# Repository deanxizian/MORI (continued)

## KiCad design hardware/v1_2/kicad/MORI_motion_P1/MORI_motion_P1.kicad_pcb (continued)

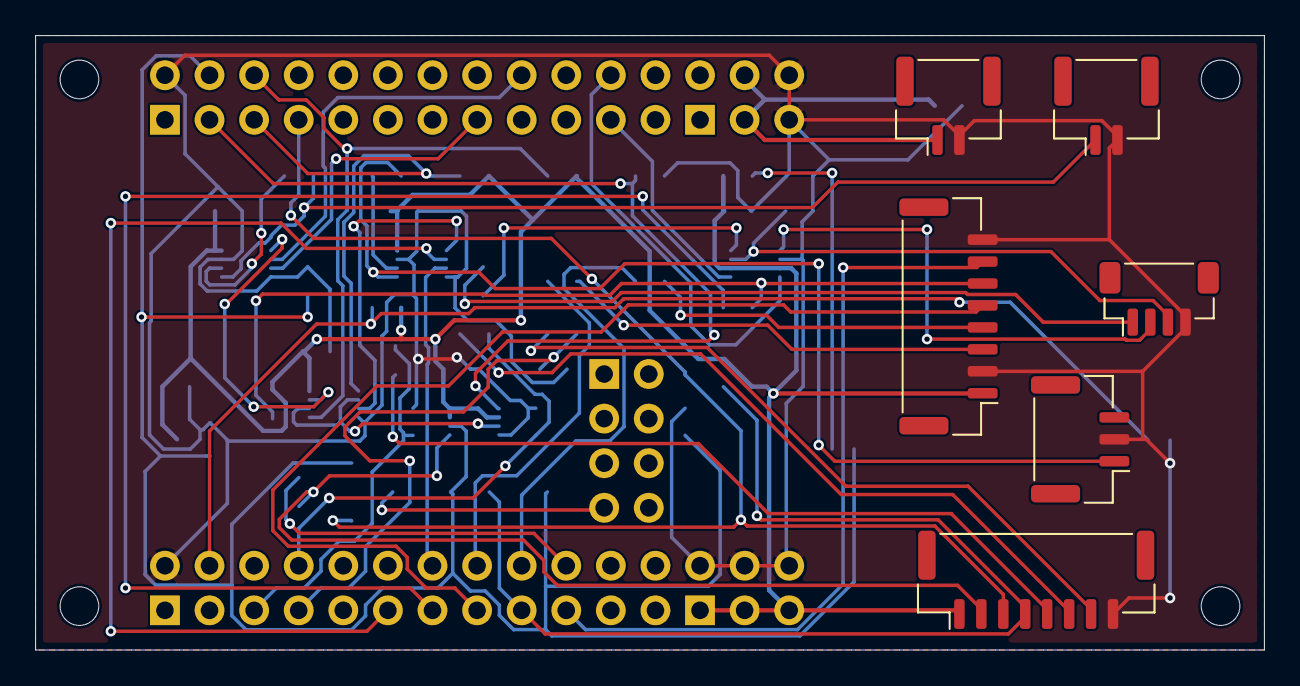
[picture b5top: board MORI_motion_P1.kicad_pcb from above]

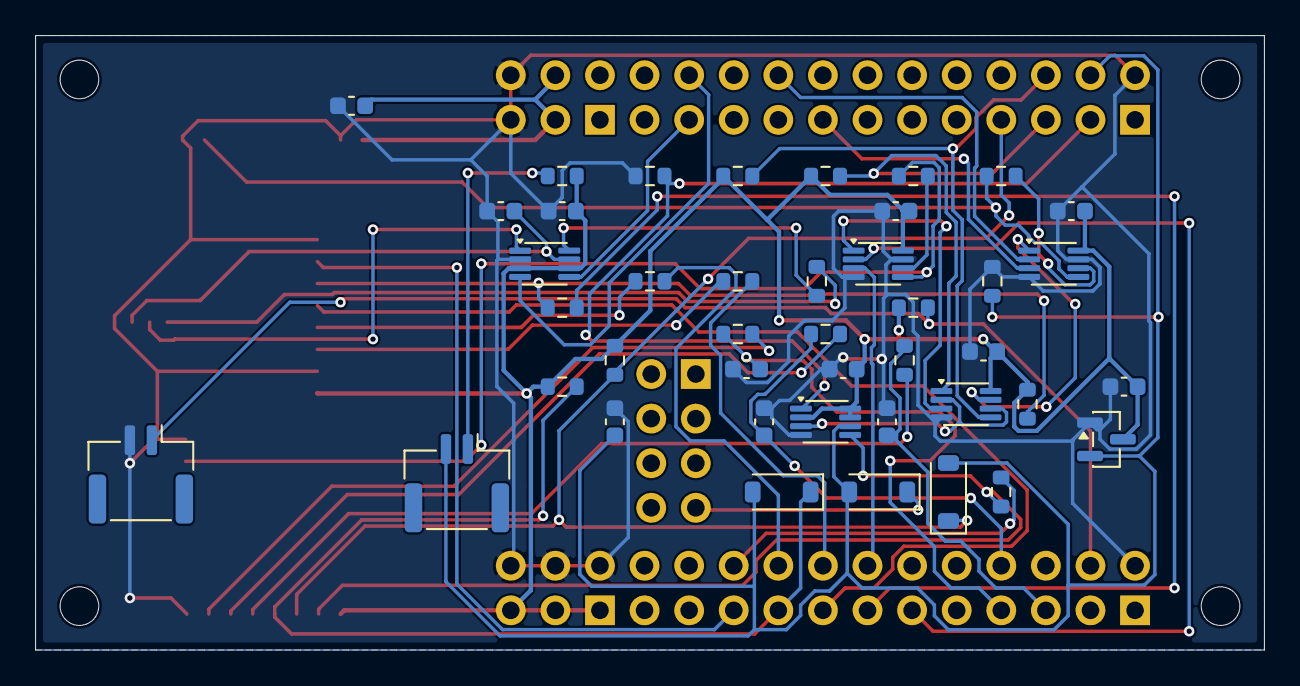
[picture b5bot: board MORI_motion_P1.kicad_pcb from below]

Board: 2 copper layers, 70.0 x 35.0 mm, 53 parts (42 on the bottom side), 45 nets.

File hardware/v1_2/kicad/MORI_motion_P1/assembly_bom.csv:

ref,value,footprint,source,note
U100,WeAct STM32F412RET6 64Pin V1.1,MORI_Custom:WeAct_F4_64Pin_V11,https://github.com/WeActStudio/WeActStudio.STM32F4_64Pin_CoreBoard,"A=P1 B=P2 C=P3 D=P4 E=P5. Complete module footprint; manufacturer drawing, NOT measured. P5 SWD accessible from module top; E7 reset tap only."
J1,MOTION 5V IN,Connector_JST:JST_GH_BM02B-GHS-TBT_1x02-1MP_P1.25mm_Vertical,,Pin numbers are PCB connector numbers; harness mating view must be continuity checked.
J2,S288 DATA ONLY,Connector_JST:JST_GH_BM02B-GHS-TBT_1x02-1MP_P1.25mm_Vertical,,Pin numbers are PCB connector numbers; harness mating view must be continuity checked.
J3,HEAD DATA ONLY,Connector_JST:JST_GH_BM03B-GHS-TBT_1x03-1MP_P1.25mm_Vertical,,Pin numbers are PCB connector numbers; harness mating view must be continuity checked.
J4,BODY IMU SPI,Connector_JST:JST_GH_BM08B-GHS-TBT_1x08-1MP_P1.25mm_Vertical,,Pin numbers are PCB connector numbers; harness mating view must be continuity checked.
J5,CAM J11 MATCH,Connector_JST:JST_SH_BM04B-SRSS-TB_1x04-1MP_P1.00mm_Vertical,,Pin numbers are PCB connector numbers; harness mating view must be continuity checked.
J6,USER BUTTON,Connector_JST:JST_GH_BM02B-GHS-TBT_1x02-1MP_P1.25mm_Vertical,,Pin numbers are PCB connector numbers; harness mating view must be continuity checked.
J7,POWER CONTROL,Connector_JST:JST_GH_BM08B-GHS-TBT_1x08-1MP_P1.25mm_Vertical,,Pin numbers are PCB connector numbers; harness mating view must be continuity checked.
J8,LATCHED ENABLE LOOP,Connector_JST:JST_GH_BM02B-GHS-TBT_1x02-1MP_P1.25mm_Vertical,,Pin numbers are PCB connector numbers; harness mating view must be continuity checked.
U1,SN74LVC2G125DCUR,Package_SO:VSSOP-8_2.3x2mm_P0.5mm,https://www.ti.com/lit/ds/symlink/sn74lvc2g125.pdf,Ioff; bus input 0..5.5V. External actuator VIH/VOH not yet verified. Default no transmission.
U2,SN74LVC2G125DCUR,Package_SO:VSSOP-8_2.3x2mm_P0.5mm,https://www.ti.com/lit/ds/symlink/sn74lvc2g125.pdf,Ioff; bus input 0..5.5V. External actuator VIH/VOH not yet verified. Default no transmission.
U3,SN74LVC2G32DCUR,Package_SO:VSSOP-8_2.3x2mm_P0.5mm,https://www.ti.com/lit/ds/symlink/sn74lvc2g32.pdf,
U4,TXU0202DCUR,Package_SO:VSSOP-8_2.3x2mm_P0.5mm,https://www.ti.com/lit/ds/symlink/txu0202.pdf,"VCC isolation and Ioff; J11.3 powers only translator B rail, never feeds motion regulator."
U5,SN74LVC1G74DCUR,Package_SO:VSSOP-8_2.3x2mm_P0.5mm,https://www.ti.com/lit/ds/symlink/sn74lvc1g74.pdf,Physical loop + supervisor + faults clear latch; only a new explicit ARM rising edge re-enables.
U6,TLV803EA29DBZR,Package_TO_SOT_SMD:SOT-23,https://www.ti.com/lit/ds/symlink/tlv803e.pdf,"2.93V threshold,200ms reset; exact non-R/non-V pinout."
D1,"BAT54H,115",Diode_SMD:D_SOD-123,,"Cathode pin1; pulls latch clear low, does not reset MCU on ordinary disable."
D2,"BAT54H,115",Diode_SMD:D_SOD-123,,"Cathode pin1; pulls latch clear low, does not reset MCU on ordinary disable."
D3,"BAT54H,115",Diode_SMD:D_SOD-123,,"Cathode pin1; pulls latch clear low, does not reset MCU on ordinary disable."
R1,68,Resistor_SMD:R_0603_1608Metric,,
R2,68,Resistor_SMD:R_0603_1608Metric,,
R3,10k,Resistor_SMD:R_0603_1608Metric,,
R4,10k,Resistor_SMD:R_0603_1608Metric,,
R5,10k,Resistor_SMD:R_0603_1608Metric,,
R6,1k,Resistor_SMD:R_0603_1608Metric,,
R7,10k,Resistor_SMD:R_0603_1608Metric,,
R8,10k,Resistor_SMD:R_0603_1608Metric,,
R9,47,Resistor_SMD:R_0603_1608Metric,,
R10,33,Resistor_SMD:R_0603_1608Metric,,
R11,33,Resistor_SMD:R_0603_1608Metric,,
R12,33,Resistor_SMD:R_0603_1608Metric,,
R13,10k,Resistor_SMD:R_0603_1608Metric,,
R14,1k,Resistor_SMD:R_0603_1608Metric,,
R15,1k,Resistor_SMD:R_0603_1608Metric,,
R16,1k,Resistor_SMD:R_0603_1608Metric,,
R17,10k,Resistor_SMD:R_0603_1608Metric,,
R18,10k,Resistor_SMD:R_0603_1608Metric,,
R19,1k,Resistor_SMD:R_0603_1608Metric,,
C1,100n,Capacitor_SMD:C_0603_1608Metric,,
C2,100n,Capacitor_SMD:C_0603_1608Metric,,
C3,100n,Capacitor_SMD:C_0603_1608Metric,,
C4,100n,Capacitor_SMD:C_0603_1608Metric,,
C5,100n,Capacitor_SMD:C_0603_1608Metric,,
C6,100n,Capacitor_SMD:C_0603_1608Metric,,
C7,100n,Capacitor_SMD:C_0603_1608Metric,,
C8,10u,Capacitor_SMD:C_0603_1608Metric,,
C9,10n,Capacitor_SMD:C_0603_1608Metric,,
C10,10n,Capacitor_SMD:C_0603_1608Metric,,
C11,10n,Capacitor_SMD:C_0603_1608Metric,,
C12,100n,Capacitor_SMD:C_0603_1608Metric,,
H1,M2 clearance,MountingHole:MountingHole_2.2mm_M2,,
H2,M2 clearance,MountingHole:MountingHole_2.2mm_M2,,
H3,M2 clearance,MountingHole:MountingHole_2.2mm_M2,,
H4,M2 clearance,MountingHole:MountingHole_2.2mm_M2,,

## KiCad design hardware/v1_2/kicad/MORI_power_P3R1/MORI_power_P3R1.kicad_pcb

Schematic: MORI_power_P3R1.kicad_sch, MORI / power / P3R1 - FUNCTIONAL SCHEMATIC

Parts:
C1, C20, C40: 100n; C_0603_1608Metric
C2: 1u 25V; C_0603_1608Metric__P3_C2
C10: Panasonic EEU-FR1C102 1000uF 16V; CP_Radial_D10.0mm_P5.00mm__P2_C10__P3_C10__P3R1_C10
C21, C41: 10n; C_0603_1608Metric
C30: Panasonic EEU-FR1C102 1000uF 16V; CP_Radial_D10.0mm_P5.00mm__P3_C30__P3R1_C30
C60: 22u / 25V / X7R; C_1210_3225Metric__P3_C60__P3R1_C60
C61, C62, C71, C72: 100n / 50V / X7R; C_0603_1608Metric
C63, C64, C66, C73, C76: 22u / 25V / X7R; C_1210_3225Metric
C65: 75p / 50V / C0G; C_0603_1608Metric
C70: 22u / 25V / X7R; C_1210_3225Metric__P3_C70
C74: 22u / 25V / X7R; C_1210_3225Metric__P3_C74
C75: 75p / 50V / C0G; C_0603_1608Metric__P3R1_C75
D1, D20, D40: BZT52H-C10,115; D_SOD-123F
D10: B540C-13-F; D_SMC__P3_D10__P3R1_D10
D30: B540C-13-F; D_SMC
F60: 1A / 125V / very fast; Fuse_Littelfuse-NANO2-451_453
F70: 2A / 125V / very fast; Fuse_Littelfuse-NANO2-451_453
H1, H2, H3, H4: M2 mounting / POSITION TBD; MountingHole_2.2mm_M2
J1: PACK AFTER 6.3A FUSE / MASTER; AMASS_XT30UPB-M_1x02_P5.0mm_Vertical__P3_J1
J2: WHEEL BUCK VIN; AMASS_XT30UPB-M_1x02_P5.0mm_Vertical__P3_J2__P3R1_J2
J3: WHEEL BUCK 9V RETURN; AMASS_XT30UPB-M_1x02_P5.0mm_Vertical__P3R1_J3
J4: HEAD BUCK VIN; AMASS_XT30UPB-M_1x02_P5.0mm_Vertical__P2_J4__P3_J4
J5: HEAD BUCK 6V RETURN; AMASS_XT30UPB-M_1x02_P5.0mm_Vertical__P2_J5__P3_J5
J6: RAW BAT SERVICE / DNP; AMASS_XT30UPB-M_1x02_P5.0mm_Vertical__P3_J6; not fitted
J7: S288 L; JST_XH_B3B-XH-A_1x03_P2.50mm_Vertical__P2_J7__P3_J7__P3R1_J7
J8: S288 R; JST_XH_B3B-XH-A_1x03_P2.50mm_Vertical__P2_J8__P3R1_J8
J9: SCS0009 CHAIN; JST_XH_B3B-XH-A_1x03_P2.50mm_Vertical
J10: MOTION CONTROL; JST_GH_BM08B-GHS-TBT_1x08-1MP_P1.25mm_Vertical__P2_J10__P3_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
J11: WHEEL DUMP 5R6 EXTERNAL; AMASS_XT30UPB-M_1x02_P5.0mm_Vertical
J12: HEAD DUMP 10R EXTERNAL; AMASS_XT30UPB-M_1x02_P5.0mm_Vertical__P2_J12
J13: S288 DATA; JST_GH_BM02B-GHS-TBT_1x02-1MP_P1.25mm_Vertical__P2_J13
J14: HEAD DATA; JST_GH_BM03B-GHS-TBT_1x03-1MP_P1.25mm_Vertical
J15: CHARGE INTERLOCK; JST_GH_BM02B-GHS-TBT_1x02-1MP_P1.25mm_Vertical
J16: CHARGER RAW VBUS SENSE; JST_GH_BM02B-GHS-TBT_1x02-1MP_P1.25mm_Vertical__P2_J16__P3R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
J17: MOTION 5V OUT / 1+ 2GND; JST_GH_BM02B-GHS-TBT_1x02-1MP_P1.25mm_Vertical__P3_J17
J18: CAM 5V OUT / 1+ 2GND; JST_XH_B2B-XH-A_1x02_P2.50mm_Vertical
JP60: SERVICE OFF / OPEN=ON; PinHeader_1x02_P2.54mm_Vertical__P3_JP60__P3R1_JP60
JP70: SERVICE OFF / OPEN=ON; PinHeader_1x02_P2.54mm_Vertical
L60, L70: 10uH / SRP7050TA-100M; Bourns_SRP7050TA_8p4_span_2p5_gap
Q1, Q10, Q30: AO4407A; SOIC-8_3.9x4.9mm_P1.27mm
Q11, Q20, Q31, Q40: AO3400A; SOT-23
Q50: MMBT3904LT1G; SOT-23
R1, R10, R30, R54: 10k; R_0603_1608Metric
R2: WSL2512R0100FEA 10mR 1% 1W; R_2512_6332Metric
R3, R4: 0; R_0603_1608Metric
R11, R31: 100; R_0603_1608Metric
R20, R24, R40, R44: 2.2k; R_0603_1608Metric
R21: 33.2k 0.1%; R_0603_1608Metric
R22, R26, R42, R46: 10k 0.1%; R_0603_1608Metric
R23, R43: 1M 0.1%; R_0603_1608Metric
R25: 37.4k 0.1%; R_0603_1608Metric
R41: 16.5k 0.1%; R_0603_1608Metric
R45: 18.7k 0.1%; R_0603_1608Metric
R50, R52: 100k 0.1%; R_0603_1608Metric
R51, R53: 27k 0.1%; R_0603_1608Metric
R55: 47k; R_0603_1608Metric
R56: 100k; R_0603_1608Metric
R60, R70: 100k / 0.1%; R_0603_1608Metric
R61: 13.3k / 0.1%; R_0603_1608Metric
R71: 13.3k / 0.1%; R_0603_1608Metric__P3_R71
TP60: +5V_MOTION; TestPoint_Pad_D1.5mm__P3_TP60
TP61, TP71: GND; TestPoint_Pad_D1.5mm
TP70: +5V_CAM; TestPoint_Pad_D1.5mm__P3R1_TP70
U1: INA180A1IDBVR; SOT-23-5
U20, U40: LM393BDR; SOIC-8_3.9x4.9mm_P1.27mm
U21, U41: TL431BIDBZR; SOT-23
U60, U70: TPS54302DDCR; TI_DDC0006A_TPS54302

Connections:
/+3V3: C1.1, J10.1, U1.5 (VS)
/+5V_CAM: C73.1, C74.1, C75.1, J18.1 (5V_OUT), L70.2, R70.1, TP70.1
/+5V_MOTION: C63.1, C64.1, C65.1, J17.1 (5V_OUT), L60.2, R60.1, TP60.1
/ARM_Q: J10.2, Q11.1, Q31.1, R54.1
/BAT_ADC: J10.5, R50.2, R51.1
/BAT_IN: J1.2 (PLUS), Q1.5, Q1.6, Q1.7, Q1.8
/BAT_MON: C2.1, F60.1, F70.1, J2.2 (PLUS), J4.2 (PLUS), J6.2 (PLUS), R2.2, R4.1, R50.1
/BAT_REV: D1.1, Q1.1 (SOURCE PROTECTED OUTPUT), Q1.2, Q1.3, R2.1, R3.1
/C5_BOOT: C72.1, U70.6 (BOOT)
/C5_EN: JP70.1 (EN), U70.5 (EN)
/C5_FB: C75.2, R70.2, R71.1, U70.4 (FB)
/C5_SW: C72.2, L70.1, U70.2 (SW)
/C5_VIN: C70.1, C71.1, C76.1, F70.2, U70.3 (VIN)
/CHG_BASE: Q50.1 (B), R55.2, R56.1
/CHG_N: J10.4, J15.1, Q50.3 (C)
/CURRENT_ADC: J10.7, U1.1 (OUT)
/FAULT_N: J10.3, U20.7 (OUT2), U40.7 (OUT2)
/GND: C1.2, C2.2, C10.2, C20.2, C21.2, C30.2, C40.2, C41.2, C60.2, C61.2, C63.2, C64.2, C66.2, C70.2, C71.2, C73.2, C74.2, C76.2, D20.2, D40.2, J1.1 (MINUS), J2.1 (MINUS), J3.1 (MINUS), J4.1 (MINUS), J5.1 (MINUS), J6.1 (MINUS), J7.1 (GND), J8.1 (GND), J9.1 (GND), J10.8, J13.2, J14.2, J15.2, J16.2, J17.2 (GND), J18.2 (GND), JP60.2 (GND), JP70.2 (GND), Q11.2, Q20.2, Q31.2, Q40.2, Q50.2 (E), R1.2, R22.2, R26.2, R42.2, R46.2, R51.2, R53.2, R54.2, R56.2, R61.2, R71.2, TP61.1, TP71.1, U1.2 (GND), U20.4 (GND), U21.3 (A), U40.4 (GND), U41.3 (A), U60.1 (GND), U70.1 (GND)
/H6_IN: D30.2, J5.2 (PLUS)
/H_BRAKE_GATE: D40.1, Q40.1, R43.1, R44.2, U40.1 (OUT1)
/H_BUS: J9.3 (BUS), J14.1
/H_DUMP_D: J12.1 (MINUS), Q40.3
/H_GATE: Q30.4, R30.1, R31.1
/H_GATE_LOW: Q31.3, R31.2
/H_OVSENSE: C41.1, R45.2, R46.1, U40.6 (IN2-)
/H_PRE: D30.1, Q30.1, Q30.2, Q30.3, R30.2
/H_REF: R40.2, U40.2 (IN1-), U40.5 (IN2+), U41.1 (K), U41.2 (REF)
/H_SENSE: R41.2, R42.1, R43.2, U40.3 (IN1+)
/H_VM: C30.1, C40.1, J9.2 (V+), J12.2 (PLUS), Q30.5 (DRAIN SWITCHED OUTPUT), Q30.6, Q30.7, Q30.8, R40.1, R41.1, R44.1, R45.1, U40.8 (VCC)
/KELVIN_N: R4.2, U1.4 (IN-)
/KELVIN_P: R3.2, U1.3 (IN+)
/M5_BOOT: C62.1, U60.6 (BOOT)
/M5_EN: JP60.1 (EN), U60.5 (EN)
/M5_FB: C65.2, R60.2, R61.1, U60.4 (FB)
/M5_SW: C62.2, L60.1, U60.2 (SW)
/M5_VIN: C60.1, C61.1, C66.1, F60.2, U60.3 (VIN)
/REV_GATE: D1.2, Q1.4, R1.1
/VBUS_CHARGE: J16.1, R55.1
/W9_IN: D10.2, J3.2 (PLUS)
/WHEEL_ADC: J10.6, R52.2, R53.1
/W_BRAKE_GATE: D20.1, Q20.1, R23.1, R24.2, U20.1 (OUT1)
/W_BUS: J7.3 (BUS), J8.3 (BUS), J13.1
/W_DUMP_D: J11.1 (MINUS), Q20.3
/W_GATE: Q10.4, R10.1, R11.1
/W_GATE_LOW: Q11.3, R11.2
/W_OVSENSE: C21.1, R25.2, R26.1, U20.6 (IN2-)
/W_PRE: D10.1, Q10.1, Q10.2, Q10.3, R10.2
/W_REF: R20.2, U20.2 (IN1-), U20.5 (IN2+), U21.1 (K), U21.2 (REF)
/W_SENSE: R21.2, R22.1, R23.2, U20.3 (IN1+)
/W_VM: C10.1, C20.1, J7.2 (V+), J8.2 (V+), J11.2 (PLUS), Q10.5 (DRAIN SWITCHED OUTPUT), Q10.6, Q10.7, Q10.8, R20.1, R21.1, R24.1, R25.1, R52.1, U20.8 (VCC)

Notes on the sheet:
MORI / POWER + DUAL 5V / S3 - SCHEMATIC ONLY
Power flows left to right. Supplies above, returns below. PROTOTYPE / UNVALIDATED.
01 Pack input / reverse protection / shunt
External pack, fuse and master switch precede J1. No charger on this PCB.
10mR / 1% / 1W
02 Kelvin current sense
Sense from the shunt pads. Discharge-only nominal transfer: 0.2 V/A.
03 Wheel 9 V conditioning
External buck return. Inrush, brake energy and thermal performance: NOT_TESTED.
1000u / 16V
04 Head 6 V conditioning
05 External converter input distribution
J2 -> external9V; J4 -> external6V. J6 is RAW BAT service, DNP. See blocks11/12 for logic5V.
06 Wheel rail / brake and overvoltage
Two comparators share one LM393B. External dump resistor needs pulse qualification.
LM393B / brake + fault
5R6 / 5W external
07 Head rail / brake and overvoltage
10R / 5W external
08 Voltage monitor / motion connector
Divider ratio 27 / 127. Current_ADC comes from block 02.
09 Charge insertion / VBUS sense
Sense and interlock only; no CC / PD / CC-CV charger implementation.
10 Supply boundaries / board mounting
Board outline / mounting coordinates UNFROZEN. P2 PCB does not implement blocks11/12.
Supply boundary
11 Motion 5 V / independent fused buck
Prototype: verify stability, temperature, cable drop and concurrent load. No PCB placement frozen.
1A input fuse
22u/25V
100n
100n BOOT
10uH / 4A rms
MOTION 5V
100k 0.1%
13.3k 0.1%
75p C0G
OPEN=ON / SHORT=OFF
5V probe
GND probe

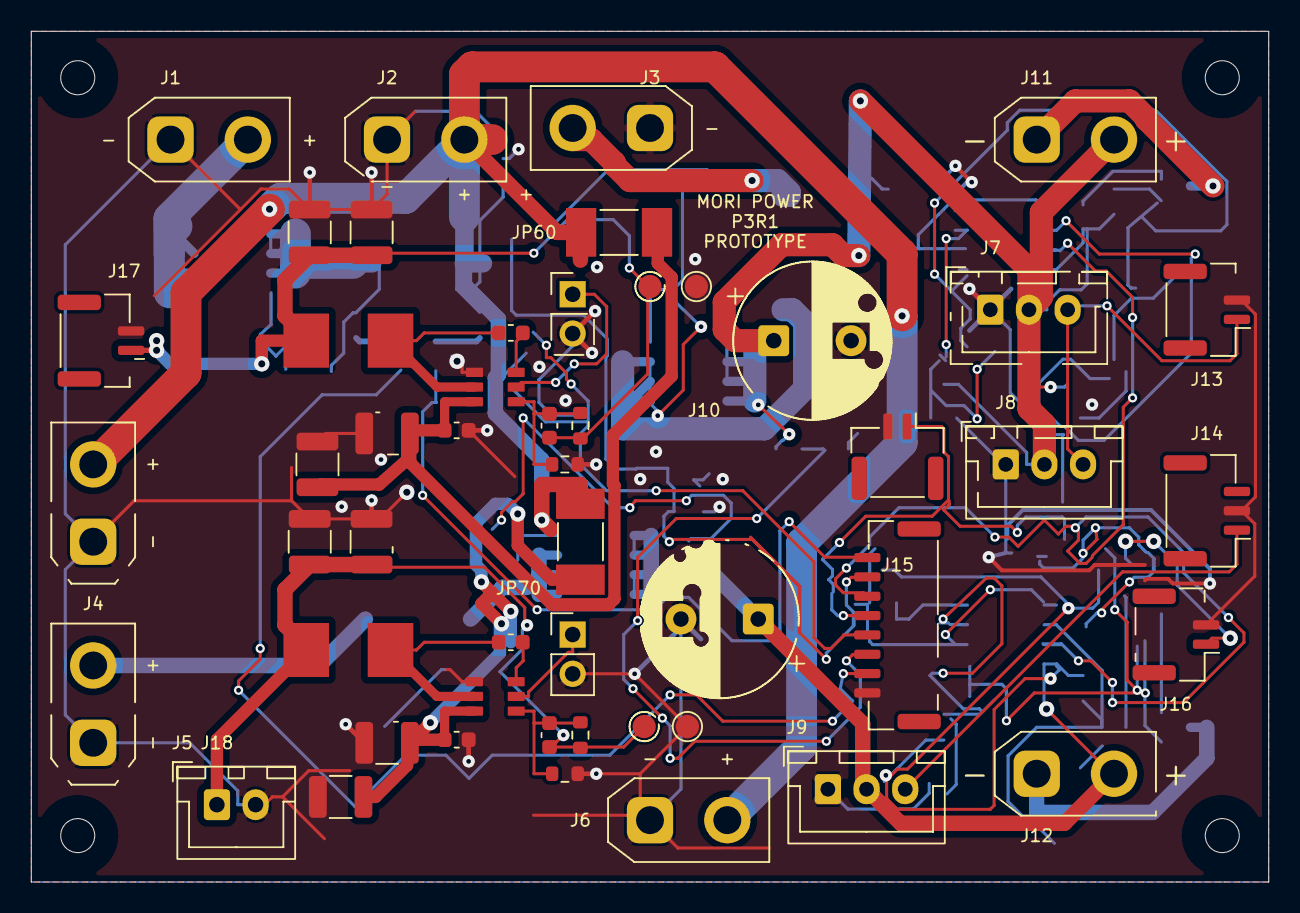
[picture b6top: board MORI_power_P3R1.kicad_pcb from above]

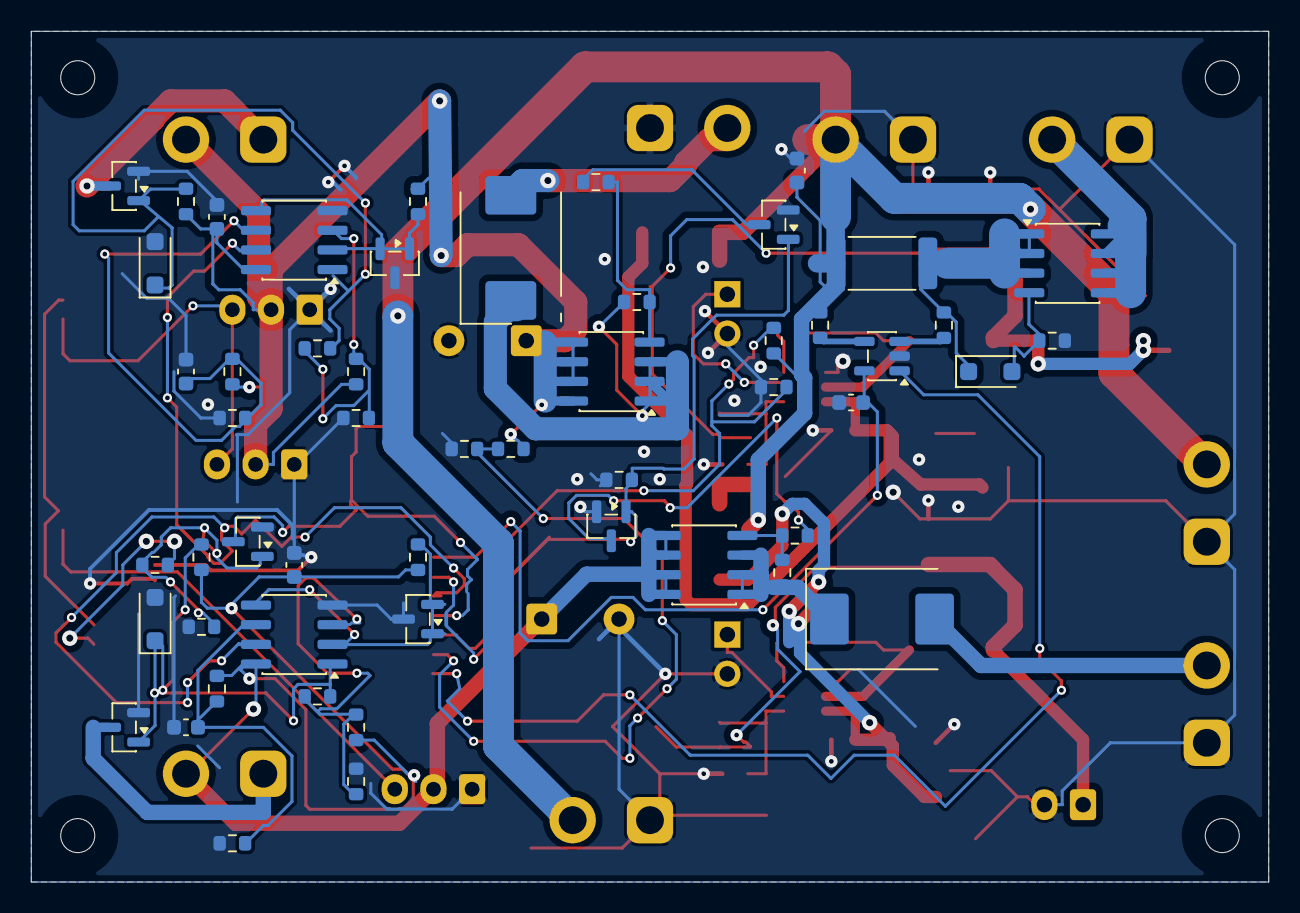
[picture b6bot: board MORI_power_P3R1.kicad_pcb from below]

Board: 2 copper layers, 80.0 x 55.0 mm, 107 parts (53 on the bottom side), 50 nets.

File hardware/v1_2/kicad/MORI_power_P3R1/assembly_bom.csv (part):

ref,value,mpn,manufacturer,footprint,lcsc,source,source_date,dnp,note
J1,PACK AFTER 6.3A FUSE / MASTER,,,MORI_Custom:AMASS_XT30UPB-M_1x02_P5.0mm_Vertical__P3_J1,,,,,"AMASS XT30UPB-M PCB: pin1 minus, pin2 plus; mating housing polarization plus continuity check mandatory."
J2,WHEEL BUCK VIN,,,MORI_Custom:AMASS_XT30UPB-M_1x02_P5.0mm_Vertical__P3_J2__P3R1_J2,,,,,"AMASS XT30UPB-M PCB: pin1 minus, pin2 plus; mating housing polarization plus continuity check mandatory."
J3,WHEEL BUCK 9V RETURN,,,MORI_Custom:AMASS_XT30UPB-M_1x02_P5.0mm_Vertical__P3R1_J3,,,,,"AMASS XT30UPB-M PCB: pin1 minus, pin2 plus; mating housing polarization plus continuity check mandatory."
J4,HEAD BUCK VIN,,,MORI_Custom:AMASS_XT30UPB-M_1x02_P5.0mm_Vertical__P2_J4__P3_J4,,,,,"AMASS XT30UPB-M PCB: pin1 minus, pin2 plus; mating housing polarization plus continuity check mandatory."
J5,HEAD BUCK 6V RETURN,,,MORI_Custom:AMASS_XT30UPB-M_1x02_P5.0mm_Vertical__P2_J5__P3_J5,,,,,"AMASS XT30UPB-M PCB: pin1 minus, pin2 plus; mating housing polarization plus continuity check mandatory."
J6,RAW BAT SERVICE / DNP,,,MORI_Custom:AMASS_XT30UPB-M_1x02_P5.0mm_Vertical__P3_J6,,,,True,Legacy external5V feed no longer used. Not5V. Leave unpopulated in S3.
J11,WHEEL DUMP 5R6 EXTERNAL,,,Connector_AMASS:AMASS_XT30UPB-M_1x02_P5.0mm_Vertical,,,,,"AMASS XT30UPB-M PCB: pin1 minus, pin2 plus; mating housing polarization plus continuity check mandatory."
J12,HEAD DUMP 10R EXTERNAL,,,MORI_Custom:AMASS_XT30UPB-M_1x02_P5.0mm_Vertical__P2_J12,,,,,"AMASS XT30UPB-M PCB: pin1 minus, pin2 plus; mating housing polarization plus continuity check mandatory."
J7,S288 L,,,MORI_Custom:JST_XH_B3B-XH-A_1x03_P2.50mm_Vertical__P2_J7__P3_J7__P3R1_J7,,,,,Board-side XH 3-pin interface only. SCS original 5264-3P uses 1GND/2VCC/3TTL. S288 factory mating plug remains unverified; adapter harness must be confirmed.
J8,S288 R,,,MORI_Custom:JST_XH_B3B-XH-A_1x03_P2.50mm_Vertical__P2_J8__P3R1_J8,,,,,Board-side XH 3-pin interface only. SCS original 5264-3P uses 1GND/2VCC/3TTL. S288 factory mating plug remains unverified; adapter harness must be confirmed.
J9,SCS0009 CHAIN,,,Connector_JST:JST_XH_B3B-XH-A_1x03_P2.50mm_Vertical,,,,,Board-side XH 3-pin interface only. SCS original 5264-3P uses 1GND/2VCC/3TTL. S288 factory mating plug remains unverified; adapter harness must be confirmed.
J10,MOTION CONTROL,,,MORI_Custom:JST_GH_BM08B-GHS-TBT_1x08-1MP_P1.25mm_Vertical__P2_J10__P3_J10__P3R1_J10,,,,,Pin numbers are PCB connector numbers; harness mating view must be continuity checked.
J13,S288 DATA,,,MORI_Custom:JST_GH_BM02B-GHS-TBT_1x02-1MP_P1.25mm_Vertical__P2_J13,,,,,Pin numbers are PCB connector numbers; harness mating view must be continuity checked.
J14,HEAD DATA,,,Connector_JST:JST_GH_BM03B-GHS-TBT_1x03-1MP_P1.25mm_Vertical,,,,,Pin numbers are PCB connector numbers; harness mating view must be continuity checked.
J15,CHARGE INTERLOCK,,,Connector_JST:JST_GH_BM02B-GHS-TBT_1x02-1MP_P1.25mm_Vertical,,,,,Pin numbers are PCB connector numbers; harness mating view must be continuity checked.
J16,CHARGER RAW VBUS SENSE,,,MORI_Custom:JST_GH_BM02B-GHS-TBT_1x02-1MP_P1.25mm_Vertical__P2_J16__P3R1_J16,,,,,Pin numbers are PCB connector numbers; harness mating view must be continuity checked.
Q1,AO4407A,,,Package_SO:SOIC-8_3.9x4.9mm_P1.27mm,,https://www.aosmd.com/sites/default/files/res/datasheets/AO4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,,,
R1,10k,,,Resistor_SMD:R_0603_1608Metric,,,,,
D1,"BZT52H-C10,115",,,Diode_SMD:D_SOD-123F,,,,,
R2,WSL2512R0100FEA 10mR 1% 1W,,,Resistor_SMD:R_2512_6332Metric,,,,,
U1,INA180A1IDBVR,,,Package_TO_SOT_SMD:SOT-23-5,,https://www.ti.com/lit/ds/symlink/ina180.pdf,,,Kelvin sense of 10mR; gain20 =>0.2V/A. Discharge only; reverse current not measured.
R3,0,,,Resistor_SMD:R_0603_1608Metric,,,,,
R4,0,,,Resistor_SMD:R_0603_1608Metric,,,,,
D10,B540C-13-F,,,MORI_Custom:D_SMC__P3_D10__P3R1_D10,,https://www.diodes.com/datasheet/download/B540C.pdf,,,B540C-13-F verified from DS13012 Rev18-2; SMC cathode pin1. Thermal/quote NOT_QUALIFIED.
Q10,AO4407A,,,Package_SO:SOIC-8_3.9x4.9mm_P1.27mm,,https://www.aosmd.com/sites/default/files/res/datasheets/AO4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,,,
Q11,AO3400A,,,Package_TO_SOT_SMD:SOT-23,,https://www.aosmd.com/sites/default/files/res/datasheets/AO3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,,,
R10,10k,,,Resistor_SMD:R_0603_1608Metric,,,,,
R11,100,,,Resistor_SMD:R_0603_1608Metric,,,,,
C10,Panasonic EEU-FR1C102 1000uF 16V,,,MORI_Custom:CP_Radial_D10.0mm_P5.00mm__P2_C10__P3_C10__P3R1_C10,,,,,"D10 x H16; height is vendor capacitor envelope, NOT fitted into old10mm allocation."
D30,B540C-13-F,,,Diode_SMD:D_SMC,,https://www.diodes.com/datasheet/download/B540C.pdf,,,B540C-13-F verified from DS13012 Rev18-2; SMC cathode pin1. Thermal/quote NOT_QUALIFIED.
Q30,AO4407A,,,Package_SO:SOIC-8_3.9x4.9mm_P1.27mm,,https://www.aosmd.com/sites/default/files/res/datasheets/AO4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,,,
Q31,AO3400A,,,Package_TO_SOT_SMD:SOT-23,,https://www.aosmd.com/sites/default/files/res/datasheets/AO3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,,,
R30,10k,,,Resistor_SMD:R_0603_1608Metric,,,,,
R31,100,,,Resistor_SMD:R_0603_1608Metric,,,,,
C30,Panasonic EEU-FR1C102 1000uF 16V,,,MORI_Custom:CP_Radial_D10.0mm_P5.00mm__P3_C30__P3R1_C30,,,,,"D10 x H16; height is vendor capacitor envelope, NOT fitted into old10mm allocation."
U20,LM393BDR,,,Package_SO:SOIC-8_3.9x4.9mm_P1.27mm,,https://www.ti.com/lit/ds/symlink/lm393b.pdf,,,
U21,TL431BIDBZR,,,Package_TO_SOT_SMD:SOT-23,,https://www.ti.com/lit/ds/symlink/tl431.pdf,,,"DBZ pin1 cathode,2 reference,3 anode. B grade +/-0.5% at25C; thermal error in tolerance model."
Q20,AO3400A,,,Package_TO_SOT_SMD:SOT-23,,https://www.aosmd.com/sites/default/files/res/datasheets/AO3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,,,
D20,"BZT52H-C10,115",,,Diode_SMD:D_SOD-123F,,,,,
R20,2.2k,,,Resistor_SMD:R_0603_1608Metric,,,,,
R21,33.2k 0.1%,,,Resistor_SMD:R_0603_1608Metric,,,,,
R22,10k 0.1%,,,Resistor_SMD:R_0603_1608Metric,,,,,
R23,1M 0.1%,,,Resistor_SMD:R_0603_1608Metric,,,,,
R24,2.2k,,,Resistor_SMD:R_0603_1608Metric,,,,,
R25,37.4k 0.1%,,,Resistor_SMD:R_0603_1608Metric,,,,,
R26,10k 0.1%,,,Resistor_SMD:R_0603_1608Metric,,,,,
C20,100n,,,Capacitor_SMD:C_0603_1608Metric,,,,,
C21,10n,,,Capacitor_SMD:C_0603_1608Metric,,,,,
U40,LM393BDR,,,Package_SO:SOIC-8_3.9x4.9mm_P1.27mm,,https://www.ti.com/lit/ds/symlink/lm393b.pdf,,,
U41,TL431BIDBZR,,,Package_TO_SOT_SMD:SOT-23,,https://www.ti.com/lit/ds/symlink/tl431.pdf,,,"DBZ pin1 cathode,2 reference,3 anode. B grade +/-0.5% at25C; thermal error in tolerance model."
Q40,AO3400A,,,Package_TO_SOT_SMD:SOT-23,,https://www.aosmd.com/sites/default/files/res/datasheets/AO3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,,,
D40,"BZT52H-C10,115",,,Diode_SMD:D_SOD-123F,,,,,
R40,2.2k,,,Resistor_SMD:R_0603_1608Metric,,,,,
R41,16.5k 0.1%,,,Resistor_SMD:R_0603_1608Metric,,,,,
R42,10k 0.1%,,,Resistor_SMD:R_0603_1608Metric,,,,,
R43,1M 0.1%,,,Resistor_SMD:R_0603_1608Metric,,,,,
R44,2.2k,,,Resistor_SMD:R_0603_1608Metric,,,,,
R45,18.7k 0.1%,,,Resistor_SMD:R_0603_1608Metric,,,,,
R46,10k 0.1%,,,Resistor_SMD:R_0603_1608Metric,,,,,
C40,100n,,,Capacitor_SMD:C_0603_1608Metric,,,,,
C41,10n,,,Capacitor_SMD:C_0603_1608Metric,,,,,
R50,100k 0.1%,,,Resistor_SMD:R_0603_1608Metric,,,,,
R51,27k 0.1%,,,Resistor_SMD:R_0603_1608Metric,,,,,
R52,100k 0.1%,,,Resistor_SMD:R_0603_1608Metric,,,,,
R53,27k 0.1%,,,Resistor_SMD:R_0603_1608Metric,,,,,
R54,10k,,,Resistor_SMD:R_0603_1608Metric,,,,,
R55,47k,,,Resistor_SMD:R_0603_1608Metric,,,,,
R56,100k,,,Resistor_SMD:R_0603_1608Metric,,,,,
C1,100n,,,Capacitor_SMD:C_0603_1608Metric,,,,,
C2,1u 25V,,,MORI_Custom:C_0603_1608Metric__P3_C2,,,,,
Q50,MMBT3904LT1G,,,Package_TO_SOT_SMD:SOT-23,,,,,SOT23 1B 2E 3C. Raw VBUS detect only; neither CC nor charging control.
H1,M2 mounting / POSITION TBD,,,MountingHole:MountingHole_2.2mm_M2,,,,,
H2,M2 mounting / POSITION TBD,,,MountingHole:MountingHole_2.2mm_M2,,,,,
H3,M2 mounting / POSITION TBD,,,MountingHole:MountingHole_2.2mm_M2,,,,,
H4,M2 mounting / POSITION TBD,,,MountingHole:MountingHole_2.2mm_M2,,,,,
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
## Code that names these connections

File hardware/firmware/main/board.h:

#pragma once
#include "driver/gpio.h"
#define PIN_BATTERY GPIO_NUM_1
#define PIN_NTC_L GPIO_NUM_2
#define PIN_NTC_R GPIO_NUM_4
#define PIN_AIN1 GPIO_NUM_5
#define PIN_AIN2 GPIO_NUM_6
#define PIN_BIN1 GPIO_NUM_7
#define PIN_BIN2 GPIO_NUM_8
#define PIN_ENC_LA GPIO_NUM_9
#define PIN_ENC_LB GPIO_NUM_10
#define PIN_ENC_RA GPIO_NUM_11
#define PIN_ENC_RB GPIO_NUM_12
#define PIN_LCD_MOSI GPIO_NUM_13
#define PIN_LCD_CLK GPIO_NUM_14
#define PIN_LCD_CS GPIO_NUM_15
#define PIN_IMU_INT GPIO_NUM_16
#define PIN_SDA GPIO_NUM_17
#define PIN_SCL GPIO_NUM_18
#define PIN_ARM GPIO_NUM_21
#define PIN_LCD_DC GPIO_NUM_39
#define PIN_LCD_RST GPIO_NUM_40
#define PIN_HEAD GPIO_NUM_41
#define PIN_HEARTBEAT GPIO_NUM_42
#define PIN_FAULT GPIO_NUM_47
#define PIN_ESTOP GPIO_NUM_48
#define MOTOR_LEFT_SIGN 1
#define MOTOR_RIGHT_SIGN -1
#define ENCODER_LEFT_SIGN 1
#define ENCODER_RIGHT_SIGN -1
#define WHEEL_M_PER_COUNT (0.000304661522567f)
